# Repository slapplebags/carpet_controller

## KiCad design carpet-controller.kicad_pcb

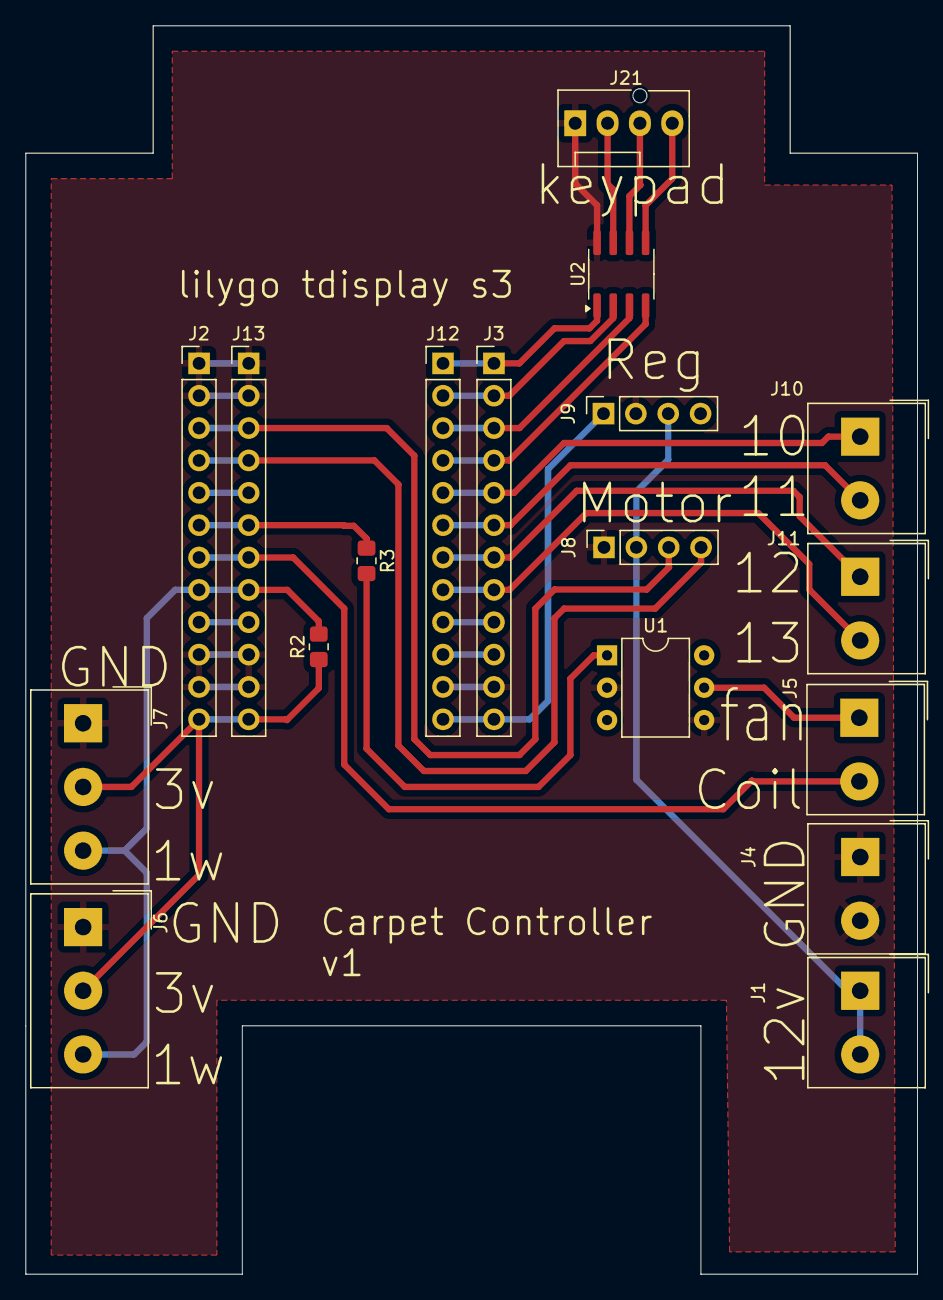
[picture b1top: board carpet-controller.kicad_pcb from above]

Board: 2 copper layers, 70.0 x 98.0 mm, 18 parts (0 on the bottom side), 22 nets.

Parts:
J1, J4, J5, J10, J11: Screw_Terminal_01x02; Altech_AK100_1x02_P5.00mm
J2, J3, J12, J13: Conn_01x12_Socket; PinHeader_1x12_P2.54mm_Vertical
J6, J7: Screw_Terminal_01x03; Altech_AK100_1x03_P5.00mm
J8, J9: Conn_01x04_Socket; PinSocket_1x04_P2.54mm_Vertical
J21: Conn_01x04_Pin; FanPinHeader_1x04_P2.54mm_Vertical
R2, R3: R_Small; R_0805_2012Metric_Pad1.20x1.40mm_HandSolder
U1: 4N35; DIP-6_W7.62mm
U2: LF398_SOIC8; SOIC-8_3.9x4.9mm_P1.27mm

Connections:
1WireData: J2.8, J6.3, J7.3, J13.8, R2.2
+3.3V: J2.12, J3.1, J6.2, J7.2, J12.1, J13.12, R2.1, U2.1 (V^{+})
+5V: J3.12, J9.1, J12.12
+12V: J1.1, J1.2, J8.2, J9.3
C Button: J21.2, U2.7 (T)
CButton: J3.4, J12.4, U2.4 (V^{-})
CoilPin: J2.7, J5.2, J13.7
Fan Relay: J5.1, U1.5
FanPin: J2.6, J13.6, R3.1
GND: J2.1, J2.2, J2.10, J2.11, J3.11, J4.1, J4.2, J6.1, J7.1, J8.1, J9.2, J12.11, J13.1, J13.2, J13.10, J13.11, J21.1, U1.2, U1.4, U2.8 (Hold)
GPIO10: J3.5, J10.1, J12.5
GPIO11: J3.6, J10.2, J12.6
GPIO12: J3.7, J11.1, J12.7
GPIO13: J3.8, J11.2, J12.8
GPIO18: J2.5, J13.5
L Button: J21.4, U2.5
LButton: J3.2, J12.2, U2.2 (Adj)
MC-CCW: J2.4, J8.4, J13.4
MC-CW: J2.3, J8.3, J13.3
unnamed: R3.2, U1.1
R Button: J21.3, U2.6 (C_{h})
RButton: J3.3, J12.3, U2.3 (I)

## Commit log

2024-03-30 carpet machine firmware
2024-04-07 added classes to make a little more readable
2025-08-28 Update carpet_controller.ino
    added dump valve control, minor changes to display settings
2026-01-31 Add initial implementation for carpet control
2026-02-05 Update HEX dump hysteresis and motor control logic
    Adjusted hysteresis value for HEX dump and modified motor control logic.
